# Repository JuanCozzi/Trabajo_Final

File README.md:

# Trabajo_Final

Trabajo final de Ingeniería Electrónica, Facultad de Ing. UBA

Control de minipiscinas 

Integrantes:
            Bourbon, Rodrigo
            Cozzi, Juan Ignacio

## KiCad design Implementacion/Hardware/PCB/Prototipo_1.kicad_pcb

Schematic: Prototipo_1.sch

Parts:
BZ1: Buzzer; Buzzer_12x9.5RM7.6
C1: 100u; CP_Elec_8x10
C3: 330uf; CP_Elec_8x10
C4, C8, C27, C29, C30, C31, C32, C33, C34, C35, C36: 10n; C_0805_2012Metric
C5, C7, C10, C37: 10u; CP_Elec_4x5.4
C6, C11, C14, C15, C17, C18, C22, C28: 100n; C_0805_2012Metric
C9: 22n; C_0805_2012Metric
C12, C13: 22p; C_0805_2012Metric
C16, C19: 1u; CP_Elec_4x5.4
C20, C23, C24, C25, C26: 10u; C_0805_2012Metric
C21: 1n; C_0805_2012Metric
D1: D_Bridge_-A+A; Diode_Bridge_Bourns_CD-DF4xxS
D2: 1N5819; D_2010_5025Metric_Pad1.52x2.65mm_HandSolder
D3: LED; D_0805_2012Metric
D4, D5: UDZSTE-175.1B; D_SOT-23_ANK
D6, D7, D8, D9, D10, D11, D12, D13, D14: 1N4007smd; D_SMA
D15: UDZSTE-175.1B; D_0805_2012Metric
F1: 507-C1Q1.5CT-ND; fuse
J1, J2, J3, J4, J5, J6, J7, J8, J9, J10, J11: Conn_01x02_Male; TerminalBlock_bornier-2_P5.08mm
J12: Conn_01x02_Male; PinSocket_1x02_P2.54mm_Vertical
L1: ASPI-6045S 330uH; L_12x12mm_H6mm
Q1: BC848; SOT-23
Q2, Q3, Q4, Q5, Q6, Q7, Q8, Q9, Q10: MMBT3906; SOT-23
R1, R8, R9, R13, R14, R24, R26, R28, R30, R32, R33, R34, R35, R36, R37, R39, R41, R43, R46, R47, R48: 1k; R_0805_2012Metric
R2, R10, R15, R17, R19, R21: 1k8; R_0805_2012Metric
R3: 3k3; R_0805_2012Metric
R4, R5, R6, R7, R11, R16, R18, R20, R22, R50, R51, R52, R53, R54: 10k; R_0805_2012Metric
R12, R23, R25, R27, R29, R31, R38, R40, R42: 740; R_0805_2012Metric
RV1: V33MLA1206NH; RV_Disc_D7mm_W3.4mm_P5mm
U1: LM2596S-ADJ; TO-263-5_TabPin3
U2: NodeMCU; DIP-30_1090_ELL
U3: ATmega328-PU; DIP-28_W7.62mm_LongPads
U4: ACS712xLCTR-05B; SOIC-8_3.9x4.9mm_P1.27mm
U5, U6, U7, U8, U9, U10, U11, U12, U13, U14, U15, U16, U17, U18: EL817; DIP-4_W7.62mm_LongPads
Y1: 16Mhz; Crystal_HC49-U_Vertical

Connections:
5V: BZ1.1 (-), C3.1, C4.1, C7.2, C8.2, C9.1, C10.1, C11.1, C22.1, L1.1, R5.1, R6.1, R7.1, R11.1, R16.1, R18.1, R20.1, R22.1, U1.4, U2.15, U3.7, U3.21, U4.1 (IP+), U4.2 (IP+), U4.8 (VCC)
24acV1: F1.2, J6.1
24acV1_F: D1.4, F1.1, RV1.2, U6.2, U7.2, U8.2, U9.2, U10.2
24acV2: D1.2, J6.2, RV1.1
A0: C14.1, R8.2, U3.27
A1: C17.1, R9.2, U3.28
Comun_salida_i: C28.1, C37.1, D6.1 (K), D7.1 (K), D8.1 (K), D9.1 (K), D10.1 (K), D11.1 (K), D12.1 (K), D13.1 (K), D14.1 (K), Q2.2, Q3.2, Q4.2, Q5.2, Q6.2, Q7.2, Q8.2, Q9.2, Q10.2, R14.1, R33.1, R34.1, R35.1, R36.1, R37.1, R46.1, R47.1, R48.1, U4.3 (IP-), U4.4 (IP-)
Corriente: U3.26, U4.7 (VIOUT)
E1: C20.2, R50.1, U3.12
E2: C23.2, R52.1, U3.13
E3: C24.2, R53.1, U3.14
E4: C25.2, R51.1, U3.15
E5: C26.2, R54.1, U3.16
Entrada_1: J7.2, R10.1
Entrada_2: J8.1, R15.1
Entrada_3: J8.2, R17.1
Entrada_4: J9.1, R19.1
Entrada_5: J9.2, R21.1
GND: C1.2, C3.2, C4.2, C5.2, C6.2, C7.1, C8.1, C10.2, C11.2, C12.1, C13.1, C14.2, C15.2, C16.2, C17.2, C18.2, C19.2, C20.1, C21.2, C22.2, C23.1, C24.1, C25.1, C26.1, C27.1, C28.2, C29.1, C30.1, C31.1, C32.1, C33.1, C34.1, C35.1, C36.1, C37.2, D1.1, D2.2 (A), D4.2 (A), D5.2 (A), D15.2 (A), J1.1, J10.2, J11.2, Q1.2 (E), R1.1, R3.1, U1.3, U1.5, U2.2, U2.10, U2.14, U2.17, U2.24, U3.8, U3.22, U4.5 (GND), U5.2, U5.3, U6.3, U7.3, U8.3, U9.3, U10.3, U11.2, U11.3, U12.2, U12.3, U13.2, U13.3, U14.2, U14.3, U15.2, U15.3, U16.2, U16.3, U17.2, U17.3, U18.2, U18.3
unnamed: BZ1.2 (+), Q1.3 (C)
unnamed: C1.1, D1.3, D15.1 (K), U1.1
unnamed: C5.1, C6.1, U2.11
unnamed: C9.2, U3.20
unnamed: C12.2, U3.9, Y1.2
unnamed: C13.2, U3.10, Y1.1
unnamed: C21.1, U4.6 (FILTER)
unnamed: D2.1 (K), L1.2, U1.2
unnamed: D3.1 (K), R1.2
unnamed: D3.2 (A), U2.4
unnamed: Q1.1 (B), R4.1
unnamed: Q2.1, R13.1
unnamed: Q3.1, R24.1
unnamed: Q4.1, R26.1
unnamed: Q5.1, R28.1
unnamed: Q6.1, R30.1
unnamed: Q7.1, R32.1
unnamed: Q8.1, R39.1
unnamed: Q9.1, R41.1
unnamed: Q10.1, R43.1
unnamed: R2.1, R3.2, U2.19
unnamed: R4.2, U3.11
unnamed: R5.2, U3.1
unnamed: R10.2, U6.1
unnamed: R11.2, R50.2, U6.4
unnamed: R12.2, U5.1
unnamed: R13.2, R14.2, U5.4
unnamed: R15.2, U7.1
unnamed: R16.2, R52.2, U7.4
unnamed: R17.2, U8.1
unnamed: R18.2, R53.2, U8.4
unnamed: R19.2, U9.1
unnamed: R20.2, R51.2, U9.4
unnamed: R21.2, U10.1
unnamed: R22.2, R54.2, U10.4
unnamed: R23.2, U11.1
unnamed: R24.2, R33.2, U11.4
unnamed: R25.2, U12.1
unnamed: R26.2, R34.2, U12.4
unnamed: R27.2, U13.1
unnamed: R28.2, R35.2, U13.4
unnamed: R29.2, U14.1
unnamed: R30.2, R36.2, U14.4
unnamed: R31.2, U15.1
unnamed: R32.2, R37.2, U15.4
unnamed: R38.2, U16.1
unnamed: R39.2, R46.2, U16.4
unnamed: R40.2, U17.1
unnamed: R41.2, R47.2, U17.4
unnamed: R42.2, U18.1
unnamed: R43.2, R48.2, U18.4
Rx_ESP_5V: J12.1, R2.2, U3.3
S1: R12.1, U3.4
S2: R23.1, U3.5
S3: R25.1, U3.6
S4: R27.1, U3.25
S5: R29.1, U3.24
S6: R31.1, U3.23
S7: R38.1, U3.19
S8: R40.1, U3.18
S9: R42.1, U3.17
Salida_1: C27.2, D6.2 (A), J5.2, Q2.3
Salida_2: C29.2, D7.2 (A), J5.1, Q3.3
Salida_3: C30.2, D8.2 (A), J4.2, Q4.3
Salida_4: C31.2, D9.2 (A), J4.1, Q5.3
Salida_5: C32.2, D10.2 (A), J3.2, Q6.3
Salida_6: C33.2, D11.2 (A), J3.1, Q7.3
Salida_7: C34.2, D12.2 (A), J2.2, Q8.3
Salida_8: C35.2, D13.2 (A), J2.1, Q9.3
Salida_9: C36.2, D14.2 (A), J1.2, Q10.3
Temp_0: C15.1, C16.1, D4.1 (K), J10.1, R6.2, R8.1
Temp_1: C18.1, C19.1, D5.1 (K), J11.1, R7.2, R9.1
Tx_ESP: J12.2, U2.18, U3.2

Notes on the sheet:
Medición de corriente salida
Se repite el circuito modificando Sx y Salida_x (x = [1,10])
Se repite el circuito modificando entrada_x y E_x (x = [1,5])
Diver de entrada (x5)
Diver de Salida (x10)

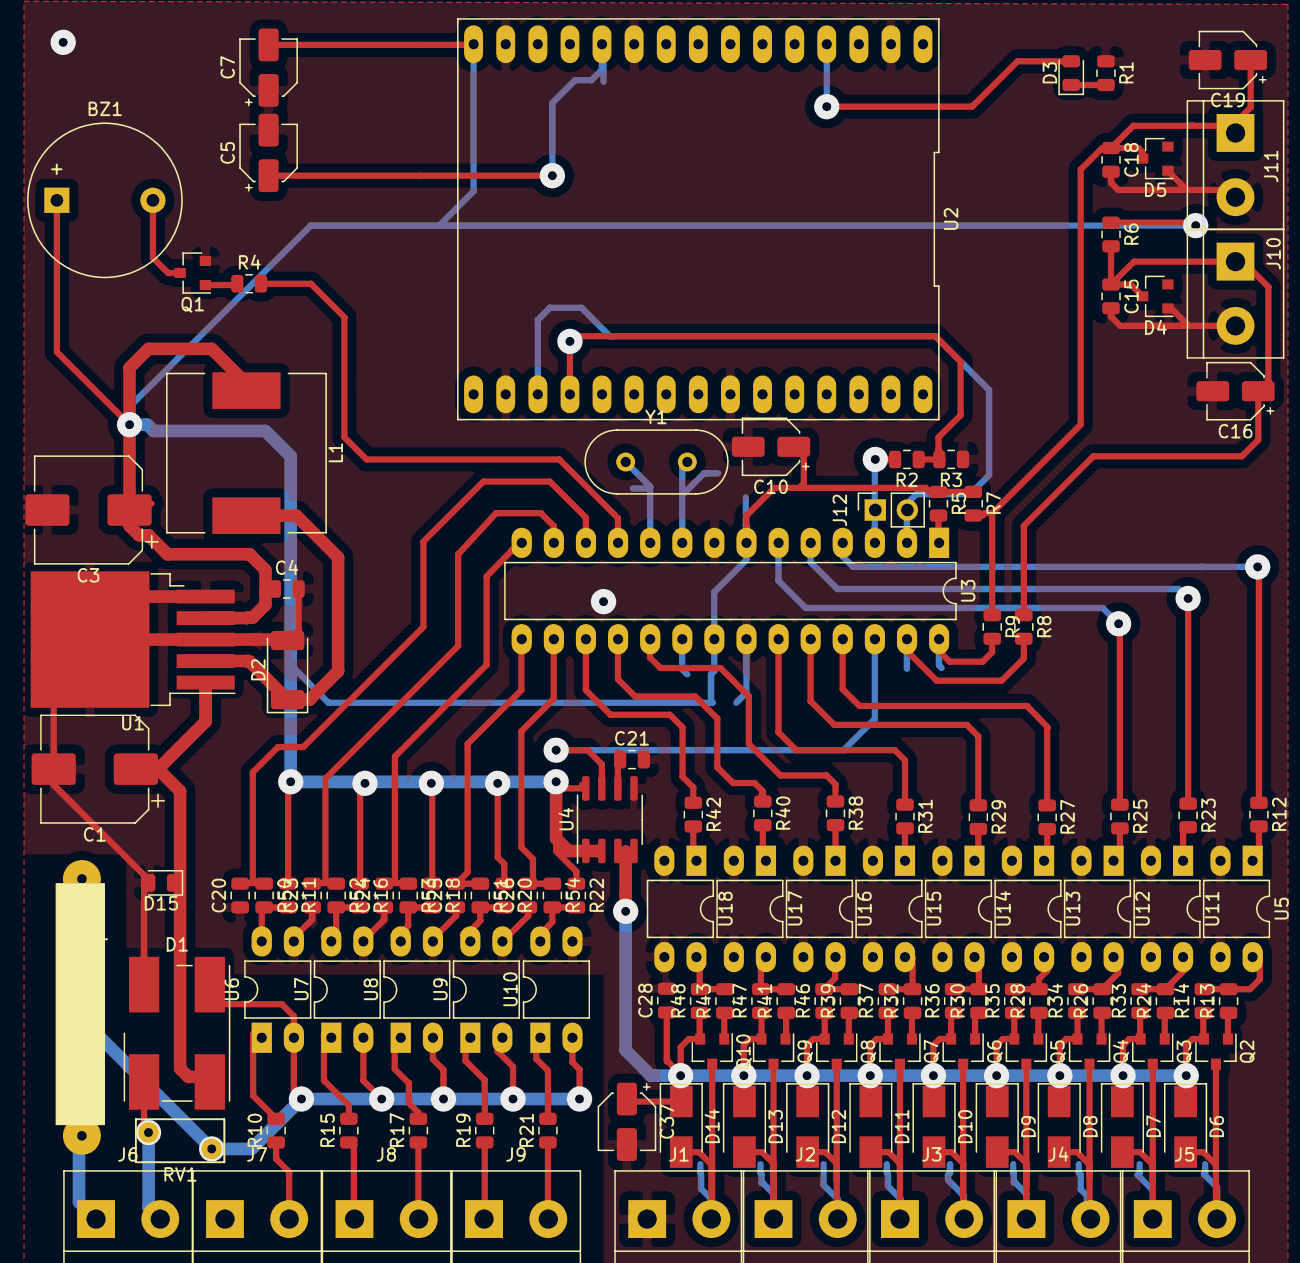
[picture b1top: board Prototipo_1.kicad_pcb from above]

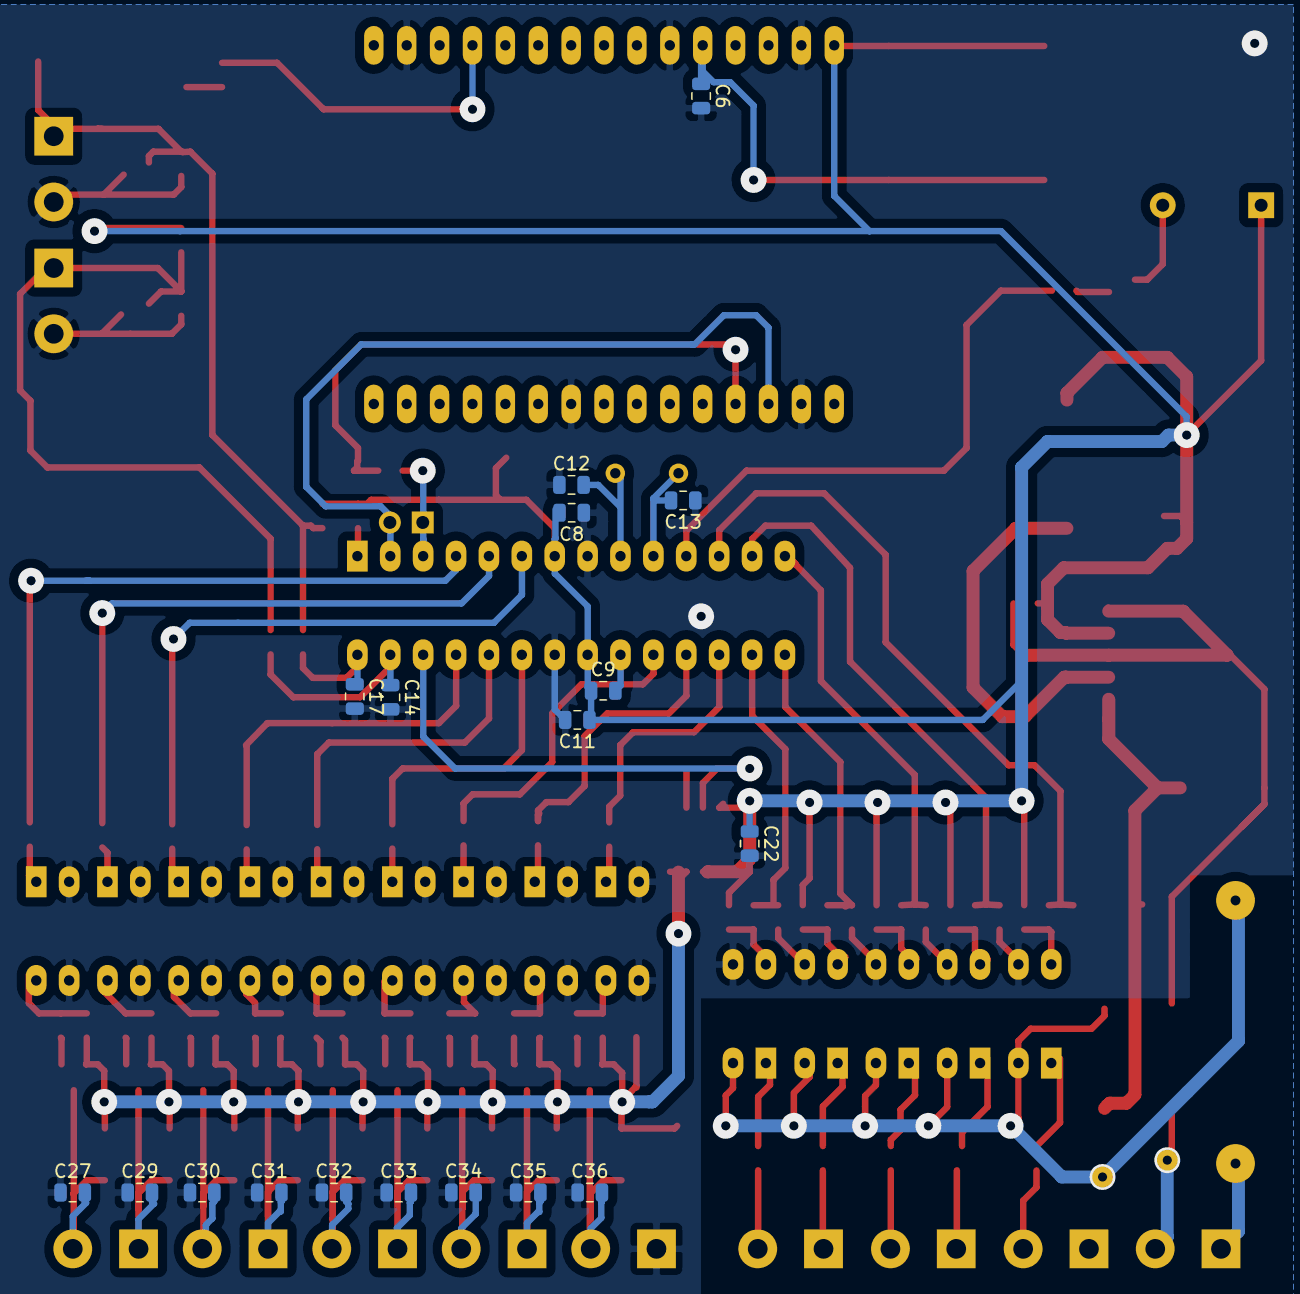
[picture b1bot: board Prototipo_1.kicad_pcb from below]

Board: 2 copper layers, 147 parts (18 on the bottom side), 92 nets.

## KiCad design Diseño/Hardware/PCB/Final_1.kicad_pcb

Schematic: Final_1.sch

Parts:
BZ1: Buzzer; Buzzer_12x9.5RM7.6
C1, C2: 100u; CP_Elec_8x10
C3: 330uf; CP_Elec_8x10
C4, C11, C21, C29, C30, C31, C32, C33, C34, C35, C36, C37: 10n; C_0805_2012Metric
C5, C6, C10: 10u; CP_Elec_4x5.4
C8, C9, C15, C16, C18, C19, C22, C24, C25, C26, C27, C28: 100n; C_0805_2012Metric
C12: 22n; C_0805_2012Metric
C13, C14: 22p; C_0805_2012Metric
C17: 1u; C_0805_2012Metric_Pad1.15x1.40mm_HandSolder
C20: 1u; C_0805_2012Metric
C23: 1n; C_0805_2012Metric
D1, D5, D6: UDZSTE-175.1B; D_0805_2012Metric
D2: MB1S; SOIC-4_4.55x2.6mm_P1.27mm
D3: 1N5819; D_SOD-123
D4: LED; LED_0805_2012Metric
D7, D8, D9, D10, D11, D12, D13, D14, D15, D16: Z0107mn; SOT-223-3_TabPin2
F1: 507-C1Q1.5CT-ND; Fuse_Bourns_MF-RHT400
J1: Entrada; TerminalBlock_bornier-3_P5.08mm
J2: l; TerminalBlock_bornier-2_P5.08mm
J3, J4, J5, J6, J9, J10: Conn_01x02_Male; TerminalBlock_bornier-2_P5.08mm
J7: transformador; TerminalBlock_bornier-3_P5.08mm
J8: Salidas a relés; TerminalBlock_bornier-3_P5.08mm
J11: SPI; PinSocket_2x03_P2.54mm_Vertical
L1: ASPI-6045S 330uH; L_Abracon_ASPI-3012S
Q1: BC848; SOT-23
R1, R2, R3, R4, R8, R9, R10, R11, R12, R15, R18, R21, R22, R23, R24, R25, R26, R27, R28: 10k; R_0805_2012Metric
R5, R19, R29, R30, R31, R32: 1k8; R_0805_2012Metric
R6: 3k3; R_0805_2012Metric
R7, R13, R14, R17, R34, R36, R38, R40, R42, R44, R46, R48, R51: 1k; R_0805_2012Metric
R16, R33, R35, R37, R39, R41, R43, R45, R47, R50: 740; R_0805_2012Metric
R20, R49, R52, R53, R54, R55, R56, R57, R58, R59: 100; R_0805_2012Metric
RV1: V33MLA1206NH; RV_Disc_D7mm_W3.6mm_P5mm
U1: LM2575-5.0BU; TO-263-5_TabPin3
U2: LM1117-3.3; SOT-223-3_TabPin2
U3: ESP-12F; ESP-12E
U4: ATmega328-AU; TQFP-32_7x7mm_P0.8mm
U5: ACS712xLCTR-05B; SOIC-8_3.9x4.9mm_P1.27mm
U6, U12, U13, U14, U15, U16, U17, U18, U19, U20: MOC3021M; SMDIP-6_W7.62mm
U7, U8, U9, U10, U11: H11AA1; SMDIP-6_W7.62mm
Y1: 16Mhz; Crystal_SMD_7050-2Pin_7.0x5.0mm

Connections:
3.3V: C6.1, C8.1, R1.2, R2.2, R3.1, R4.1, U2.2 (VO), U3.8 (VCC)
5V: BZ1.1 (-), C3.1, C4.1, C5.1, C10.2, C11.2, C12.1, C24.1, J11.1, L1.1, R10.1, R11.1, R12.1, R15.1, R21.1, R22.1, R23.1, R24.1, U1.4 (FB), U2.3 (VI), U4.4 (VCC), U4.6 (VCC), U4.20 (AREF), U5.8 (VCC)
24acV1: F1.2, J1.2
24acV1_F: D2.3 (~~), F1.1, RV1.2, U5.1 (IP+), U5.2 (IP+)
24acV2: D2.4 (~~), J1.1, J1.3, J7.1, RV1.1
AD0: C15.1, R13.2, U4.11 (PD7)
AD1: C18.1, R14.2, U4.10 (PD6)
Comun_salida_I: D7.1 (A1), D8.1 (A1), D9.1 (A1), D10.1 (A1), D11.1 (A1), D12.1 (A1), D13.1 (A1), D14.1 (A1), D15.1 (A1), D16.1 (A1), R20.2, R49.2, R52.2, R53.2, R54.2, R55.2, R56.2, R57.2, R58.2, R59.2, U5.3 (IP-), U5.4 (IP-), U7.2, U8.2, U9.2, U10.2, U11.2
Corriente: U4.22 (ADC7), U5.7 (VIOUT)
E1: C22.1, R18.1, U4.32 (PD2)
E2: C25.1, R25.1, U4.26 (PC3)
E3: C26.1, R26.1, U4.25 (PC2)
E4: C27.1, R27.1, U4.27 (PC4)
E5: C28.1, R28.1, U4.28 (PC5)
Entrada_1: J7.2, R19.1
Entrada_2: J7.3, R29.1
Entrada_3: J8.1, R30.1
Entrada_4: J8.2, R31.1
Entrada_5: J8.3, R32.1
GND: C1.2, C2.2, C3.2, C4.2, C5.2, C6.2, C8.2, C9.2, C10.1, C11.1, C13.1, C14.1, C15.2, C16.2, C17.2, C18.2, C19.2, C20.2, C22.2, C23.2, C24.2, C25.2, C26.2, C27.2, C28.2, D1.2 (A), D2.2 (-), D3.2 (A), D4.1 (K), D5.2 (A), D6.2 (A), J9.2, J10.2, J11.5, Q1.2 (E), R6.1, R8.1, U1.3 (GND), U1.5 (~ON~/OFF), U2.1 (GND), U3.15 (GND), U4.3 (GND), U4.5 (GND), U4.21 (GND), U5.5 (GND), U6.2, U7.4, U8.4, U9.4, U10.4, U11.4, U12.2, U13.2, U14.2, U15.2, U16.2, U17.2, U18.2, U19.2, U20.2
unnamed: BZ1.2 (+), Q1.3 (C)
unnamed: C1.1, C2.1, D1.1 (K), D2.1 (+), U1.1 (VIN)
unnamed: C9.1, R2.1, U3.1 (~RST)
unnamed: C12.2, U4.18 (AVCC)
unnamed: C13.2, U4.7 (XTAL1/PB6), Y1.2
unnamed: C14.2, U4.8 (XTAL2/PB7), Y1.1
unnamed: C21.2, R20.1
unnamed: C23.1, U5.6 (FILTER)
unnamed: C29.2, R49.1
unnamed: C30.2, R52.1
unnamed: C31.2, R53.1
unnamed: C32.2, R54.1
unnamed: C33.2, R55.1
unnamed: C34.2, R56.1
unnamed: C35.2, R57.1
unnamed: C36.2, R58.1
unnamed: C37.2, R59.1
unnamed: D3.1 (K), L1.2, U1.2 (OUT)
unnamed: D4.2 (A), R7.1
unnamed: D7.3 (G), U6.4
unnamed: D8.3 (G), U12.4
unnamed: D9.3 (G), U13.4
unnamed: D10.3 (G), U14.4
unnamed: D11.3 (G), U15.4
unnamed: D12.3 (G), U16.4
unnamed: D13.3 (G), U17.4
unnamed: D14.3 (G), U18.4
unnamed: D15.3 (G), U19.4
unnamed: D16.3 (G), U20.4
unnamed: Q1.1 (B), R9.1
unnamed: R1.1, U3.3 (EN)
unnamed: R3.2, U3.18 (GPIO0)
unnamed: R4.2, U3.17 (GPIO2)
unnamed: R5.1, R6.2, U3.21 (GPIO3/RXD)
unnamed: R7.2, U3.7 (GPIO13)
unnamed: R8.2, U3.16 (GPIO15)
unnamed: R9.2, U4.9 (PD5)
unnamed: R15.2, R18.2, U7.5
unnamed: R16.2, U6.1
unnamed: R17.2, U6.6
unnamed: R19.2, U7.1
unnamed: R21.2, R25.2, U8.5
unnamed: R22.2, R26.2, U9.5
unnamed: R23.2, R27.2, U10.5
unnamed: R24.2, R28.2, U11.5
unnamed: R29.2, U8.1
unnamed: R30.2, U9.1
unnamed: R31.2, U10.1
unnamed: R32.2, U11.1
unnamed: R33.2, U12.1
unnamed: R34.2, U12.6
unnamed: R35.2, U13.1
unnamed: R36.2, U13.6
unnamed: R37.2, U14.1
unnamed: R38.2, U14.6
unnamed: R39.2, U15.1
unnamed: R40.2, U15.6
unnamed: R41.2, U16.1
unnamed: R42.2, U16.6
unnamed: R43.2, U17.1
unnamed: R44.2, U17.6
unnamed: R45.2, U18.1
unnamed: R46.2, U18.6
unnamed: R47.2, U19.1
unnamed: R48.2, U19.6
unnamed: R50.2, U20.1
unnamed: R51.2, U20.6
RST: J11.6, R10.2, U4.29 (~RESET~/PC6)
Rx_ESP_5V: R5.2, U4.31 (PD1)
S1: R16.1, U4.2 (PD4)
S2: R33.1, U4.1 (PD3)
S3: R35.1, U4.12 (PB0)
S4: R39.1, U4.13 (PB1)
S5: R43.1, U4.14 (PB2)
S6: J11.3, R45.1, U4.15 (PB3)
S7: J11.2, R50.1, U4.16 (PB4)
S8: J11.4, R41.1, U4.17 (PB5)
S9: R37.1, U4.23 (PC0)
S10: R47.1, U4.24 (PC1)
Salida_1: C21.1, D7.2 (A2), J6.2, R17.1
Salida_2: C29.1, D8.2 (A2), J6.1, R34.1
Salida_3: C30.1, D9.2 (A2), J5.2, R36.1
Salida_4: C32.1, D11.2 (A2), J5.1, R40.1
Salida_5: C34.1, D13.2 (A2), J4.2, R44.1
Salida_6: C35.1, D14.2 (A2), J4.1, R46.1
Salida_7: C37.1, D16.2 (A2), J3.2, R51.1
Salida_8: C33.1, D12.2 (A2), J3.1, R42.1
Salida_9: C31.1, D10.2 (A2), J2.2, R38.1
Salida_10: C36.1, D15.2 (A2), J2.1, R48.1
Temp_0: C16.1, C17.1, D5.1 (K), J9.1, R11.2, R13.1
Temp_1: C19.1, C20.1, D6.1 (K), J10.1, R12.2, R14.1
Tx_ESP: U3.22 (GPIO1/TXD), U4.30 (PD0)

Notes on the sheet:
Medición de corriente salida
Se repite el circuito modificando Sx y Salida_x (x = [1,10])
Se repite el circuito modificando entrada_x y E_x (x = [1,5])
Diver de entrada (x5)
Diver de Salida (x10)
Entradas pulsador
Entrada sensores temperatura
Salidas a relés
Entrada Transformador

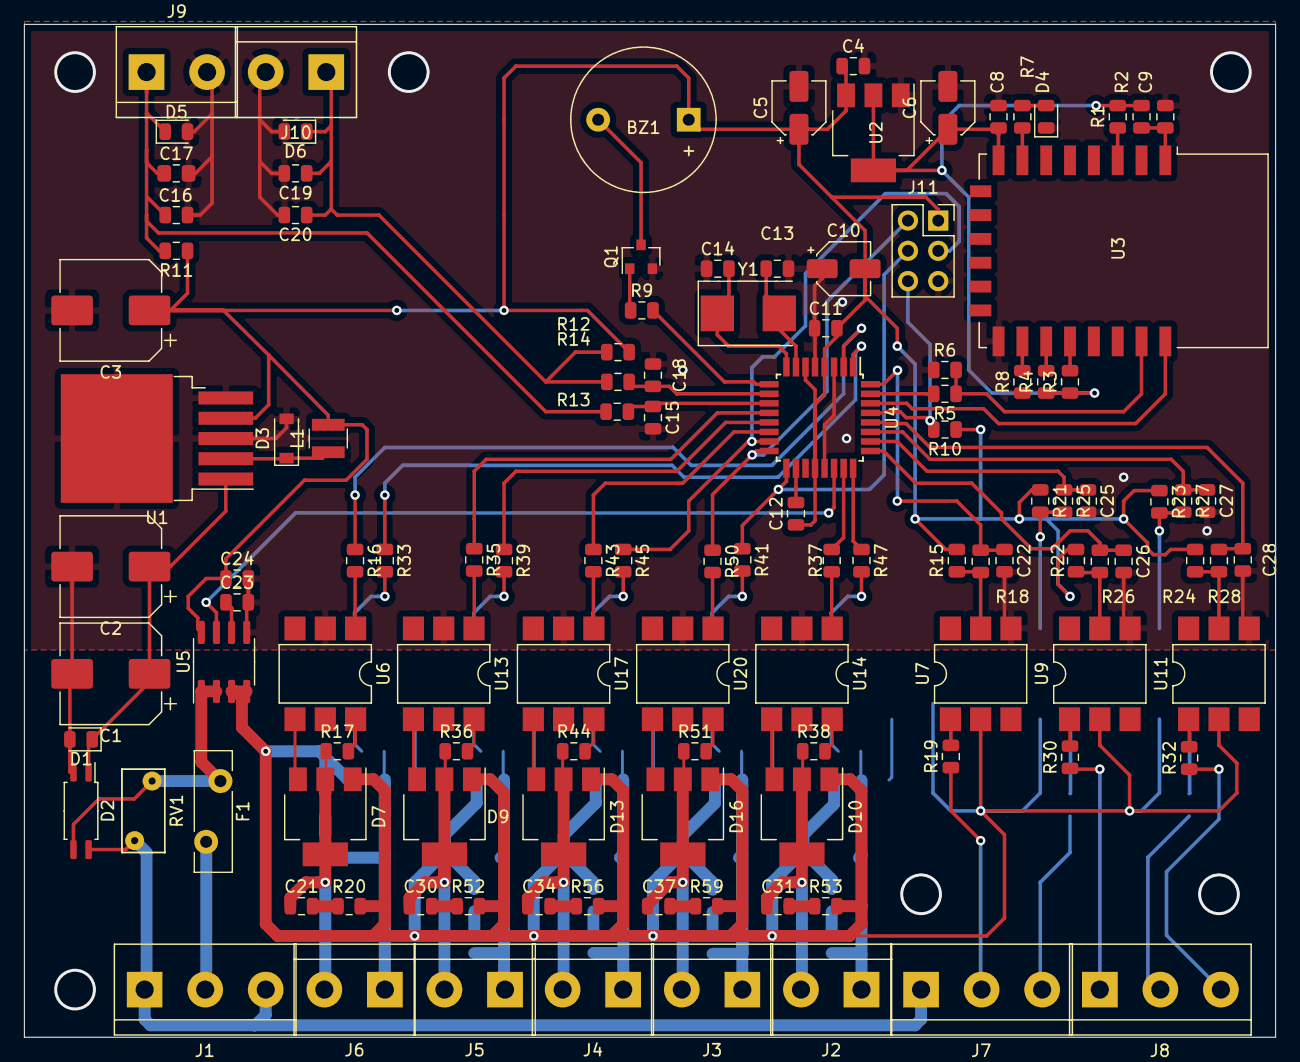
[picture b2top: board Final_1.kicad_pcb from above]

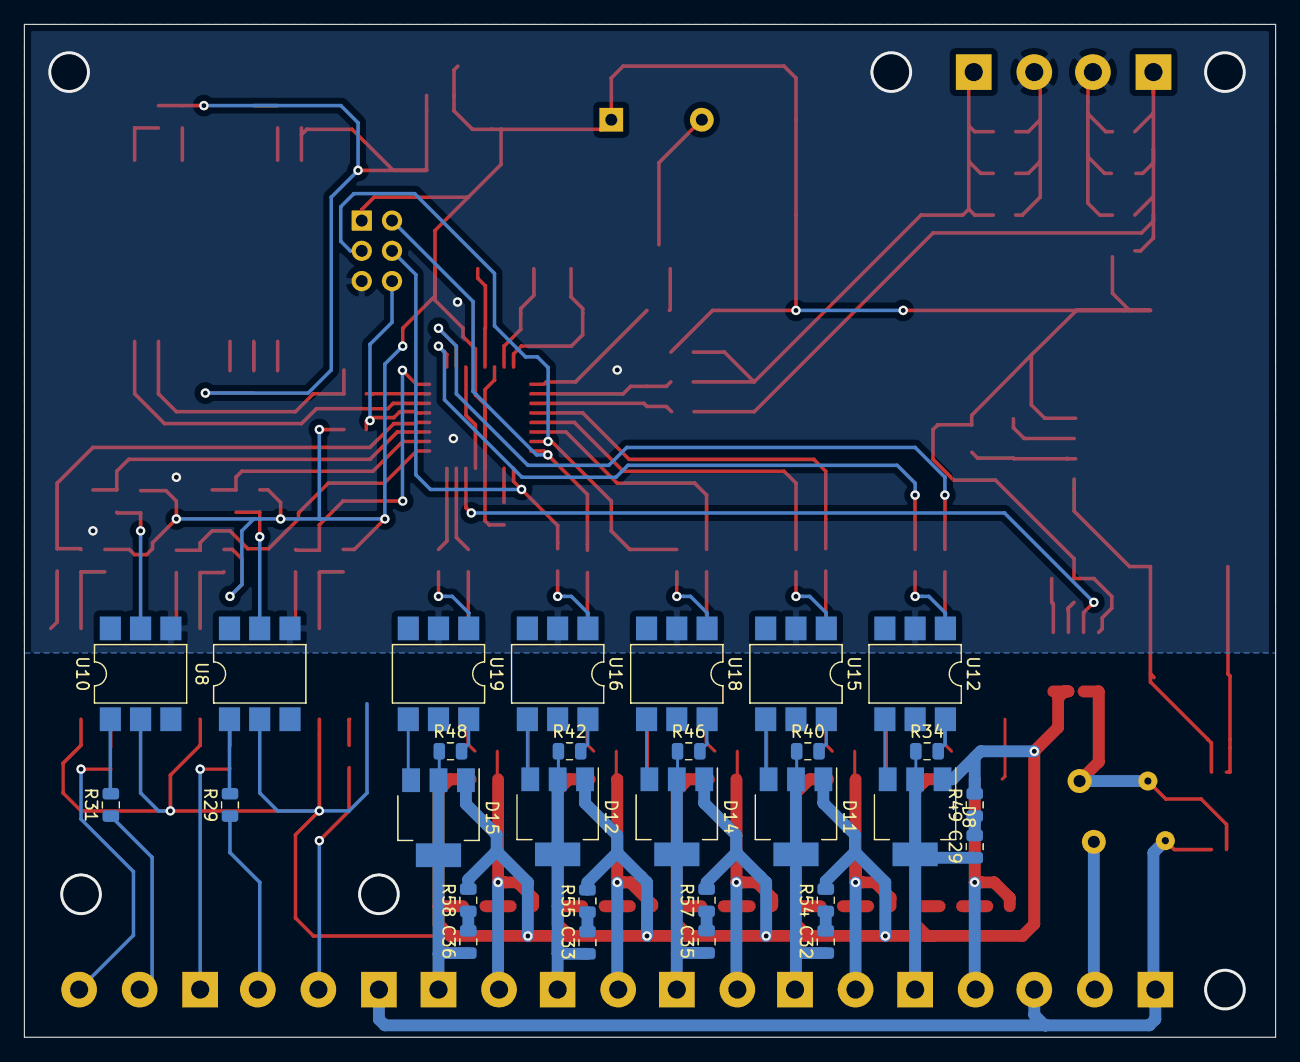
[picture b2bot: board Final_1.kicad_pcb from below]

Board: 2 copper layers, 105.0 x 85.0 mm, 148 parts (29 on the bottom side), 112 nets.

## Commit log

2020-07-24 Inicial
2020-07-24 overleaft
2020-07-24 diagrama en secuencia
2020-07-24 Planos gabinete
2020-07-25 Esquematicos y PCB
2020-07-26 Planos montaje
2020-07-27 Cuminicacion
2020-07-28 Actualización pcb
2020-08-10 imagenes
2020-08-15 Implementación inicial del webserver con muchos prints de debug (muchos), y un mock de dispositivo con autenticación para el ESP.
2020-08-15 Agregado campo indicando nombre descriptivo para las salidas.
2020-08-16 Agregado el nombre descriptivo de las salidas al dashboard de los dispositivos.
2020-08-16 Ahora el mock de dispositivo verifica si está autenticado antes de intentar la conexión del websocket.
2020-08-25 Agregadas alertas de información y error en la página web. También se agregó un programa para el ESP para probar los mensajes de forma sencilla.
2020-08-25 Agregados los diagramas de flujo de la unidad principal y de comunicación.
2020-08-27 Manual de instalación y operación
    avances
2020-09-03 manual
2020-09-12 Agregados templates para cambio de contraseña. También botón para desasociar dispositivo.
2020-09-12 Cambio en ID de dispositivo. Actualizado diagrama de secuencia.
2020-09-12 Ahora distintos dispositivos pueden registrar salidas con los mismos números como corresponde.
2020-09-26 Implementación preliminar del mecanismo de desvinculación.
2020-09-26 Cambio en la implementación del proceso de desvinculación del dispositivo y emprolijamiento del código de la unidad de comunicación.
2020-09-28 Interfaz gráfica de la unidad de comunicación finalizada.
2020-10-06 Agregado reset y cambio de contraseña.
2020-10-15 Agregado chequeo de permisos.
2020-10-15 ESP sin mock.
2020-10-17 Alerta de debug para datos de usuario en ESP.
2021-03-19 Bump django from 3.0.7 to 3.1.6 in /Implementacion/Software/webserver
    Bumps [django](https://github.com/django/django) from 3.0.7 to 3.1.6.
    - [Release notes](https://github.com/django/django/releases)
    - [Commits](https://github.com/django/django/compare/3.0.7...3.1.6)
2021-03-19 Bump djangorestframework in /Implementacion/Software/webserver
    Bumps [djangorestframework](https://github.com/encode/django-rest-framework) from 3.11.0 to 3.11.2.
    - [Release notes](https://github.com/encode/django-rest-framework/releases)
    - [Commits](https://github.com/encode/django-rest-framework/compare/3.11.0...3.11.2)
2021-03-30 Bump pygments from 2.6.1 to 2.7.4 in /Implementacion/Software/webserver
    Bumps [pygments](https://github.com/pygments/pygments) from 2.6.1 to 2.7.4.
    - [Release notes](https://github.com/pygments/pygments/releases)
    - [Changelog](https://github.com/pygments/pygments/blob/master/CHANGES)
    - [Commits](https://github.com/pygments/pygments/compare/2.6.1...2.7.4)
2021-03-30 Bump django from 3.0.7 to 3.0.12 in /Implementacion/Software/webserver
    Bumps [django](https://github.com/django/django) from 3.0.7 to 3.0.12.
    - [Release notes](https://github.com/django/django/releases)
    - [Commits](https://github.com/django/django/compare/3.0.7...3.0.12)
2021-04-08 Bump django from 3.0.7 to 3.0.14 in /Implementacion/Software/webserver
    Bumps [django](https://github.com/django/django) from 3.0.7 to 3.0.14.
    - [Release notes](https://github.com/django/django/releases)
    - [Commits](https://github.com/django/django/compare/3.0.7...3.0.14)
2021-04-20 Bump autobahn in /Implementacion/Software/webserver
    Bumps [autobahn](https://github.com/crossbario/autobahn-cpp) from 20.6.2 to 20.12.3.
    - [Release notes](https://github.com/crossbario/autobahn-cpp/releases)
    - [Commits](https://github.com/crossbario/autobahn-cpp/commits)
2021-04-20 Bump py from 1.9.0 to 1.10.0 in /Implementacion/Software/webserver
    Bumps [py](https://github.com/pytest-dev/py) from 1.9.0 to 1.10.0.
    - [Release notes](https://github.com/pytest-dev/py/releases)
    - [Changelog](https://github.com/pytest-dev/py/blob/master/CHANGELOG.rst)
    - [Commits](https://github.com/pytest-dev/py/compare/1.9.0...1.10.0)
2021-06-04 Bump django from 3.0.7 to 3.1.9 in /Implementacion/Software/webserver
    Bumps [django](https://github.com/django/django) from 3.0.7 to 3.1.9.
    - [Release notes](https://github.com/django/django/releases)
    - [Commits](https://github.com/django/django/compare/3.0.7...3.1.9)
    ---
    updated-dependencies:
    - dependency-name: django
2021-06-10 Bump django from 3.0.7 to 3.1.12 in /Implementacion/Software/webserver
    Bumps [django](https://github.com/django/django) from 3.0.7 to 3.1.12.
    - [Release notes](https://github.com/django/django/releases)
    - [Commits](https://github.com/django/django/compare/3.0.7...3.1.12)
    ---
    updated-dependencies:
    - dependency-name: django
2021-09-22 Bump django from 3.0.7 to 3.1.13 in /Implementacion/Software/webserver
    Bumps [django](https://github.com/django/django) from 3.0.7 to 3.1.13.
    - [Release notes](https://github.com/django/django/releases)
    - [Commits](https://github.com/django/django/compare/3.0.7...3.1.13)
    ---
    updated-dependencies:
    - dependency-name: django
2022-01-21 Bump ipython from 7.17.0 to 7.31.1 in /Implementacion/Software/webserver
    Bumps [ipython](https://github.com/ipython/ipython) from 7.17.0 to 7.31.1.
    - [Release notes](https://github.com/ipython/ipython/releases)
    - [Commits](https://github.com/ipython/ipython/compare/7.17.0...7.31.1)
    ---
    updated-dependencies:
    - dependency-name: ipython
2022-02-11 Bump twisted from 20.3.0 to 22.1.0 in /Implementacion/Software/webserver
    Bumps [twisted](https://github.com/twisted/twisted) from 20.3.0 to 22.1.0.
    - [Release notes](https://github.com/twisted/twisted/releases)
    - [Changelog](https://github.com/twisted/twisted/blob/trunk/NEWS.rst)
    - [Commits](https://github.com/twisted/twisted/compare/twisted-20.3.0...twisted-22.1.0)
    ---
    updated-dependencies:
2022-04-06 Bump twisted from 20.3.0 to 22.2.0 in /Implementacion/Software/webserver
    Bumps [twisted](https://github.com/twisted/twisted) from 20.3.0 to 22.2.0.
    - [Release notes](https://github.com/twisted/twisted/releases)
    - [Changelog](https://github.com/twisted/twisted/blob/trunk/NEWS.rst)
    - [Commits](https://github.com/twisted/twisted/compare/twisted-20.3.0...twisted-22.2.0)
    ---
    updated-dependencies:
2022-05-26 Bump twisted from 20.3.0 to 22.4.0 in /Implementacion/Software/webserver
    Bumps [twisted](https://github.com/twisted/twisted) from 20.3.0 to 22.4.0.
    - [Release notes](https://github.com/twisted/twisted/releases)
    - [Changelog](https://github.com/twisted/twisted/blob/trunk/NEWS.rst)
    - [Commits](https://github.com/twisted/twisted/compare/twisted-20.3.0...twisted-22.4.0)
    ---
    updated-dependencies:
2022-11-04 Bump twisted in /Implementacion/Software/webserver
    Bumps [twisted](https://github.com/twisted/twisted) from 20.3.0 to 22.10.0.
    - [Release notes](https://github.com/twisted/twisted/releases)
    - [Changelog](https://github.com/twisted/twisted/blob/trunk/NEWS.rst)
    - [Commits](https://github.com/twisted/twisted/compare/twisted-20.3.0...twisted-22.10.0)
    ---
    updated-dependencies:
